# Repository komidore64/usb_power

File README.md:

# usb_power

external usb power for your console usb devices

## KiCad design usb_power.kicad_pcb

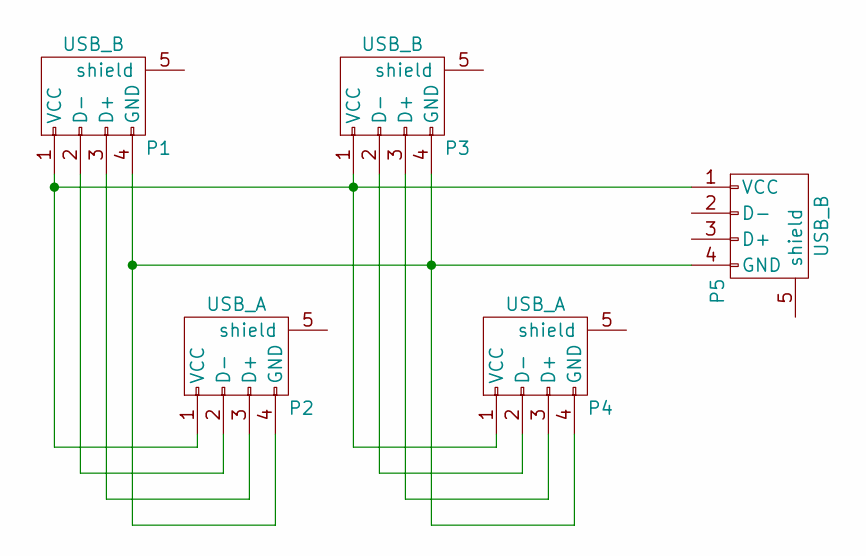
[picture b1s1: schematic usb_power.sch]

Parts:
P1, P3, P5: USB_B
P2, P4: USB_A

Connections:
unnamed: P1.1 (VCC), P2.1 (VCC), P3.1 (VCC), P4.1 (VCC), P5.1 (VCC)
unnamed: P1.2 (D-), P2.2 (D-)
unnamed: P1.3 (D+), P2.3 (D+)
unnamed: P1.4 (GND), P2.4 (GND), P3.4 (GND), P4.4 (GND), P5.4 (GND)
unnamed: P3.2 (D-), P4.2 (D-)
unnamed: P3.3 (D+), P4.3 (D+)

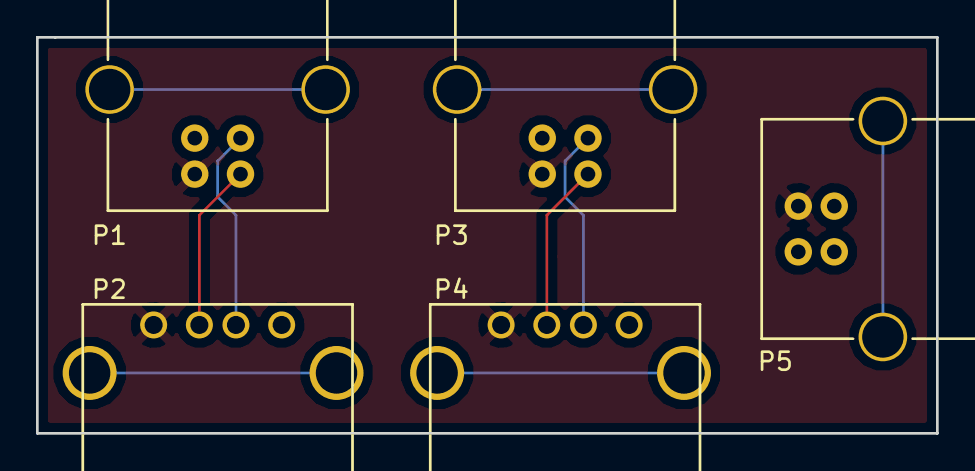
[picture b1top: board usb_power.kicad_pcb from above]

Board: 2 copper layers, 50.0 x 22.0 mm, 5 parts (0 on the bottom side), 6 nets.

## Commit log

2018-08-21 initial commit - unfinished
2018-08-21 add readme
